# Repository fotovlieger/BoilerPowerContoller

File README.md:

# BoilerPowerContoller (OBSOLETE, see BoilerController repo)
220V power controller that diverts excess solar power to an electric water boiler. Controller is interfaced to HomeAssistant

## Harware
- A simple electric boiler (no electronics, just a heating element and 'mechanical' thermostat)
- A cheap [thyristor voltage regulator](voltageregulator.md) with display and buttons
- Esp32 microcontroller
- temperature sensor to monitor water temperature

Note: the 'ground' ans signals to/from the power controler are connected to the 220V mains! Optocouplers an a power source for the esp32 are needed. (to be able to connect to its usp port while running or connect external (grounded) sensors)

## Software setup

- Main idea is to control the thyristor circuit by generating trigger pulses. Controlling the deleay of these pulses
  relative to the 50Hz zero crossing allows to control the output power to the boiler.
- Must be in C++: latency of micropython on esp32 is not good enough (must be better that 1ms, preferably 100us)
- interface to HASS: direct or via MQTT
- Implementation: based on EspHome, external component (replaces legacy 'custom component')

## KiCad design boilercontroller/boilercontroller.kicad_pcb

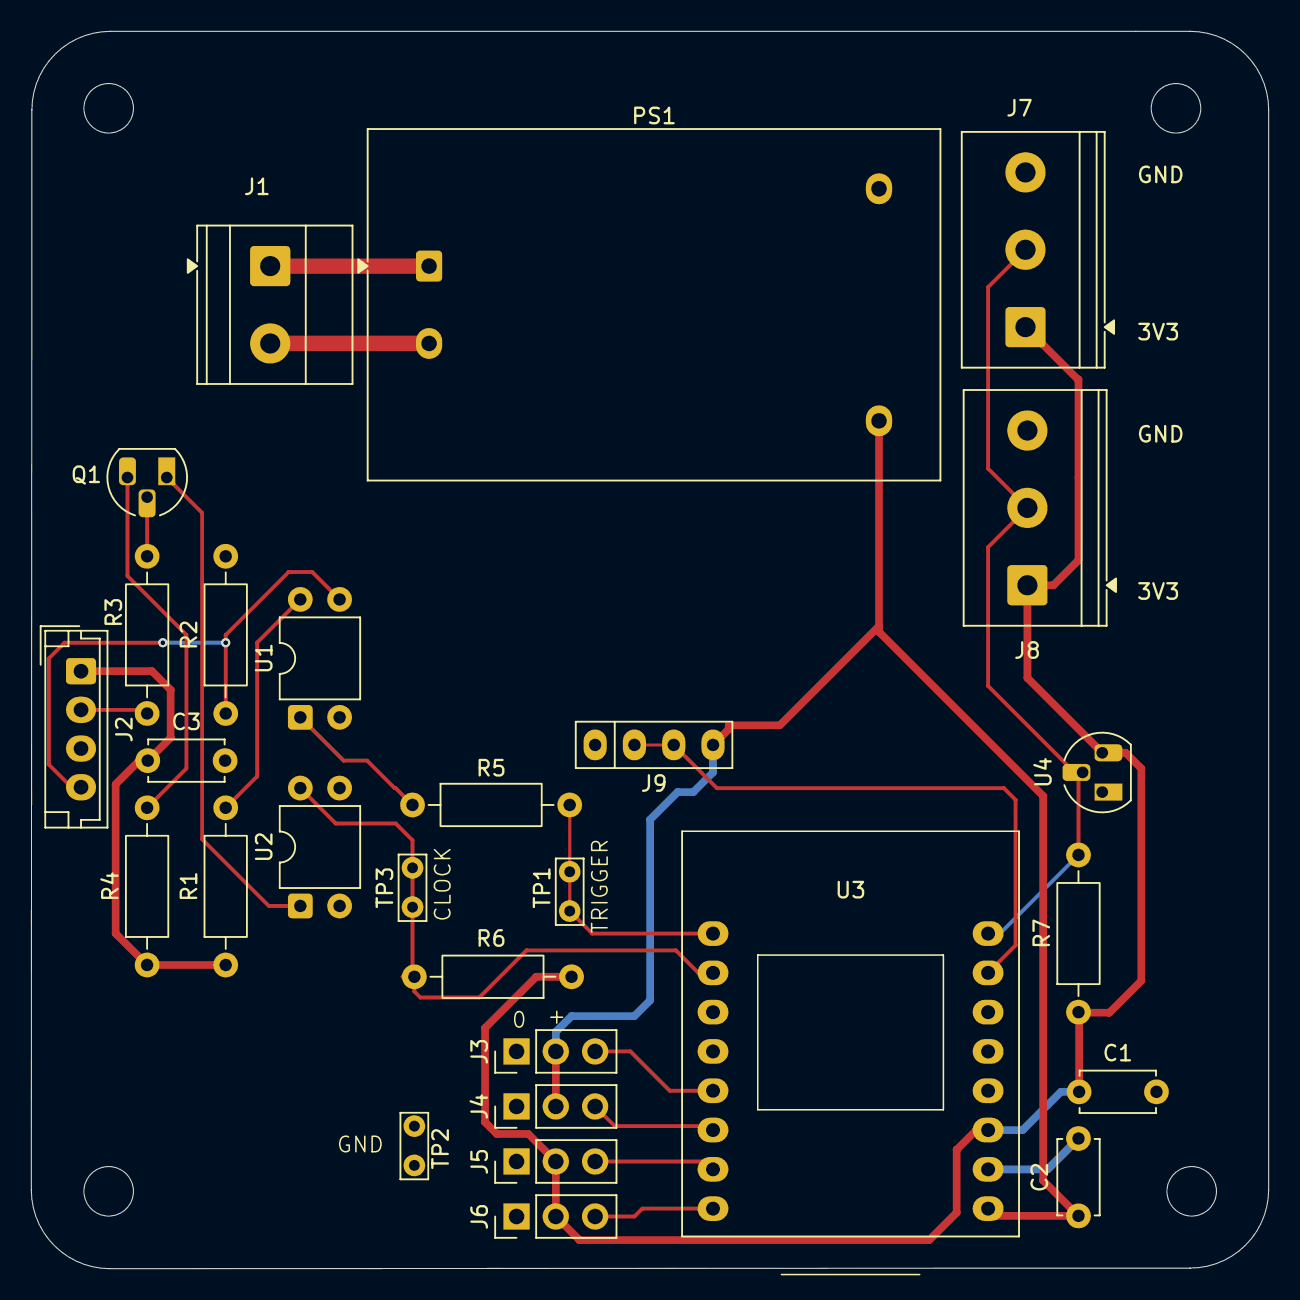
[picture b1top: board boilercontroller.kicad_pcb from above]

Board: 2 copper layers, 80.0 x 80.0 mm, 32 parts (0 on the bottom side), 22 nets.

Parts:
C1, C2, C3: 100n; C_Disc_D4.7mm_W2.5mm_P5.00mm
H1, H2, H3, H4: MountingHole; MountingHole_3.2mm_M3
J1: Screw_Terminal_01x02; TerminalBlock_Phoenix_MKDS-1,5-2_1x02_P5.00mm_Horizontal
J2: Conn_01x04_Socket; JST_EH_B4B-EH-A_1x04_P2.50mm_Vertical
J3: IO7; PinHeader_1x03_P2.54mm_Vertical
J4: IO8; PinHeader_1x03_P2.54mm_Vertical
J5: IO9; PinHeader_1x03_P2.54mm_Vertical
J6: IO10; PinHeader_1x03_P2.54mm_Vertical
J7: BOILER1; TerminalBlock_Phoenix_PT-1,5-3-5.0-H_1x03_P5.00mm_Horizontal
J8: BOILER2; TerminalBlock_Phoenix_PT-1,5-3-5.0-H_1x03_P5.00mm_Horizontal
J9: Status Leds; Pad_01x04
PS1: HLK-PM01; Converter_ACDC_Hi-Link_HLK-PMxx
Q1: 2N4401; TO-92_Hans
R1: 100; R_Axial_DIN0207_L6.3mm_D2.5mm_P10.16mm_Horizontal
R2: 2k2; R_Axial_DIN0207_L6.3mm_D2.5mm_P10.16mm_Horizontal
R3: 22k; R_Axial_DIN0207_L6.3mm_D2.5mm_P10.16mm_Horizontal
R4: 1k; R_Axial_DIN0207_L6.3mm_D2.5mm_P10.16mm_Horizontal
R5: 470; R_Axial_DIN0207_L6.3mm_D2.5mm_P10.16mm_Horizontal
R6: 10k; R_Axial_DIN0207_L6.3mm_D2.5mm_P10.16mm_Horizontal
R7: 4k7; R_Axial_DIN0207_L6.3mm_D2.5mm_P10.16mm_Horizontal
TP1, TP2, TP3: TestPoint; TestPoint_Bridge_Pitch2.54mm_Drill0.7mm
U1, U2: PC817; DIP-4_W7.62mm
U3: ESP32_C3_oled
U4: DS18B20; TO-92_Hans

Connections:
+3V3: C1.1, J5.2, J6.2, J7.1, J8.1, R6.1, R7.1, U3.11 (3V3), U4.3 (V_{DD})
+5V: C2.1, J3.2, J4.2, J9.4, PS1.4 (+Vout), U3.9 (VBus)
+5V+EXT: C3.1, J2.1, R1.1, R4.1
/CLOCK: R6.2, TP3.1, U2.4, U3.2 (D4)
/D7_5V: J3.3, U3.5 (D7)
/D8_5V: J4.3, U3.6 (D8)
/D9_3V: J5.3, U3.7 (D9)
/D10_3v: J6.3, U3.8 (D10)
/SCR: J2.4, R2.1, U1.3
/STATUS_LEDS: J9.2, J9.3, U3.15 (D1)
/TRIGGER: R5.2, TP1.1, U3.1 (D3)
/ZERO: J2.2, R3.1
GND: C1.2, C2.2, J3.1, J4.1, J5.1, J6.1, J7.3, J8.3, J9.1, PS1.3 (-Vout), TP2.1, U1.2, U2.3, U3.10 (GND), U4.1 (GND)
GND_EXT: C3.2, J2.3, R2.2, U2.2
unnamed: J1.1, PS1.1 (AC/L)
unnamed: J1.2, PS1.2 (AC/N)
unnamed: J7.2, J8.2, R7.2, U3.16 (D0), U4.2 (DQ)
unnamed: Q1.2 (B), R3.2
unnamed: Q1.3 (C), R4.2
unnamed: Q1.1 (E), U2.1
unnamed: R1.2, U1.4
unnamed: R5.1, U1.1

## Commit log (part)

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2025-10-29 Update README with hardware details
    Added hardware specifications for the project.
2025-10-29 Update README with software setup and hardware details
    Added software setup details and hardware notes.
2025-10-29 Update hardware section in README.md
    Clarified hardware description for the power controller.
2025-10-29 Create documentation for voltage regulator
    Added initial documentation for the voltage regulator.
2025-10-29 Fix link to thyristor voltage regulator documentation
2025-12-18 external component to generate pulses
2025-12-18 kicad files. todo: add libraries
2026-02-21 Revise boiler-controller configuration and sensors
    Updated boiler controller configuration with new parameters and additional temperature sensor.
2026-02-21 Format and clean up my_component.h
    just to be sure to archive the lates version
2026-02-21 Refactor MyComponent to use current_option for mode
